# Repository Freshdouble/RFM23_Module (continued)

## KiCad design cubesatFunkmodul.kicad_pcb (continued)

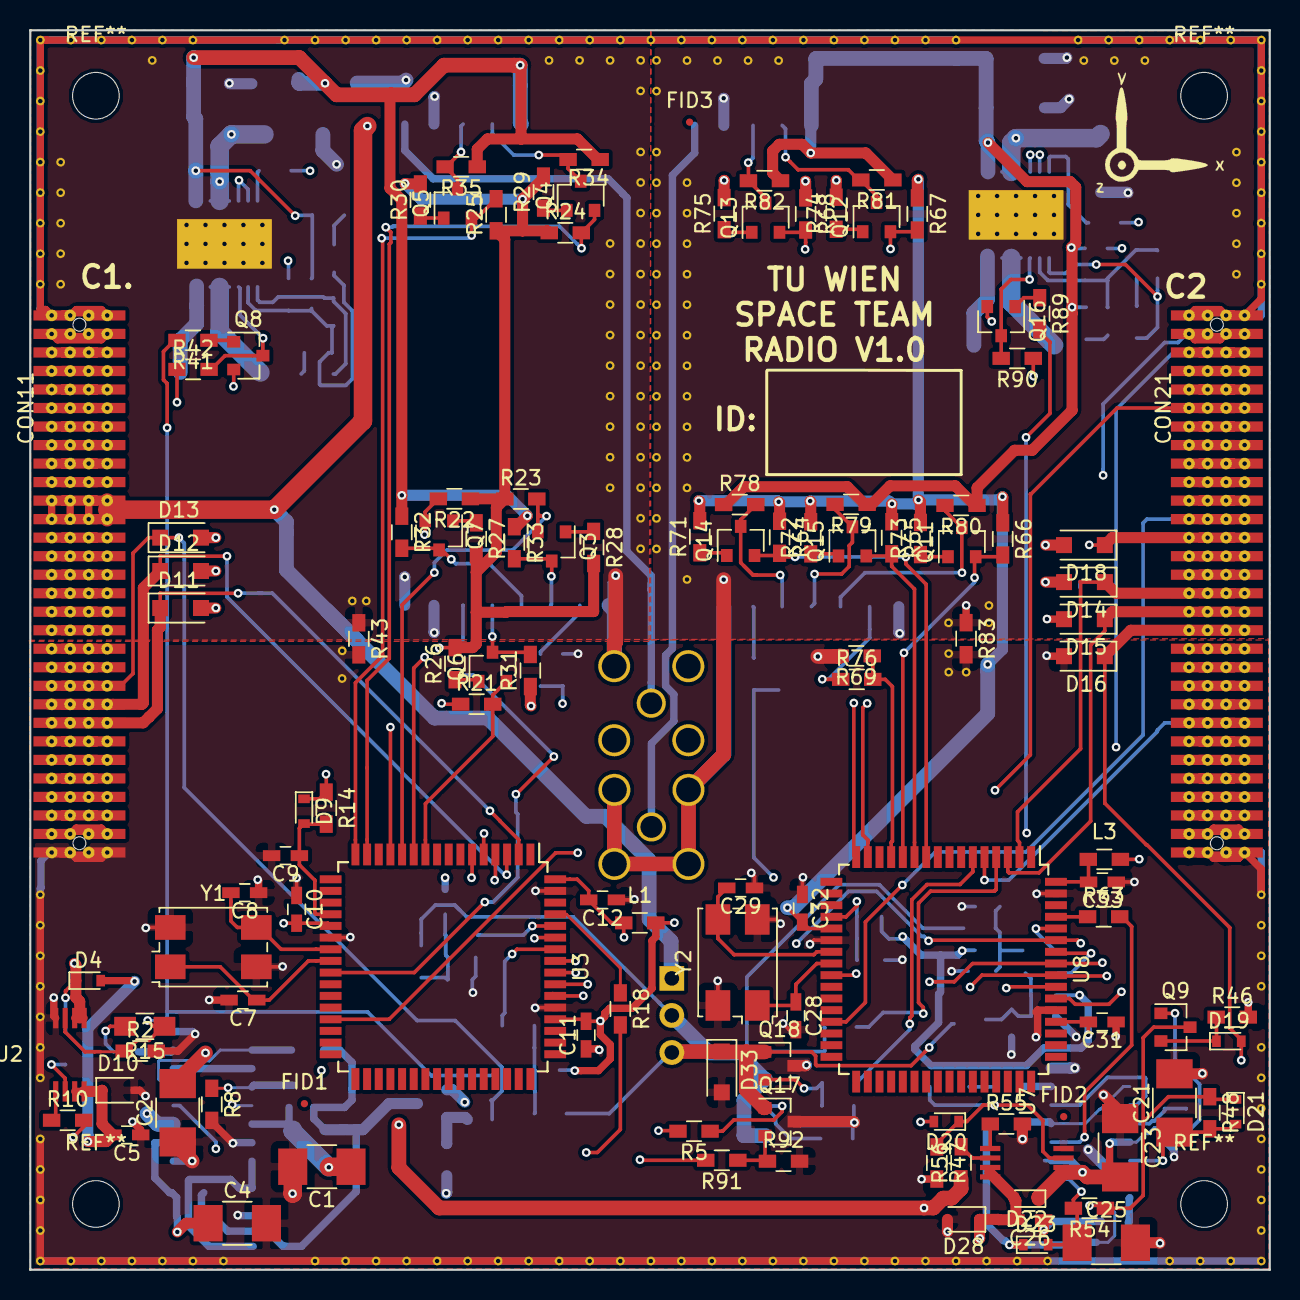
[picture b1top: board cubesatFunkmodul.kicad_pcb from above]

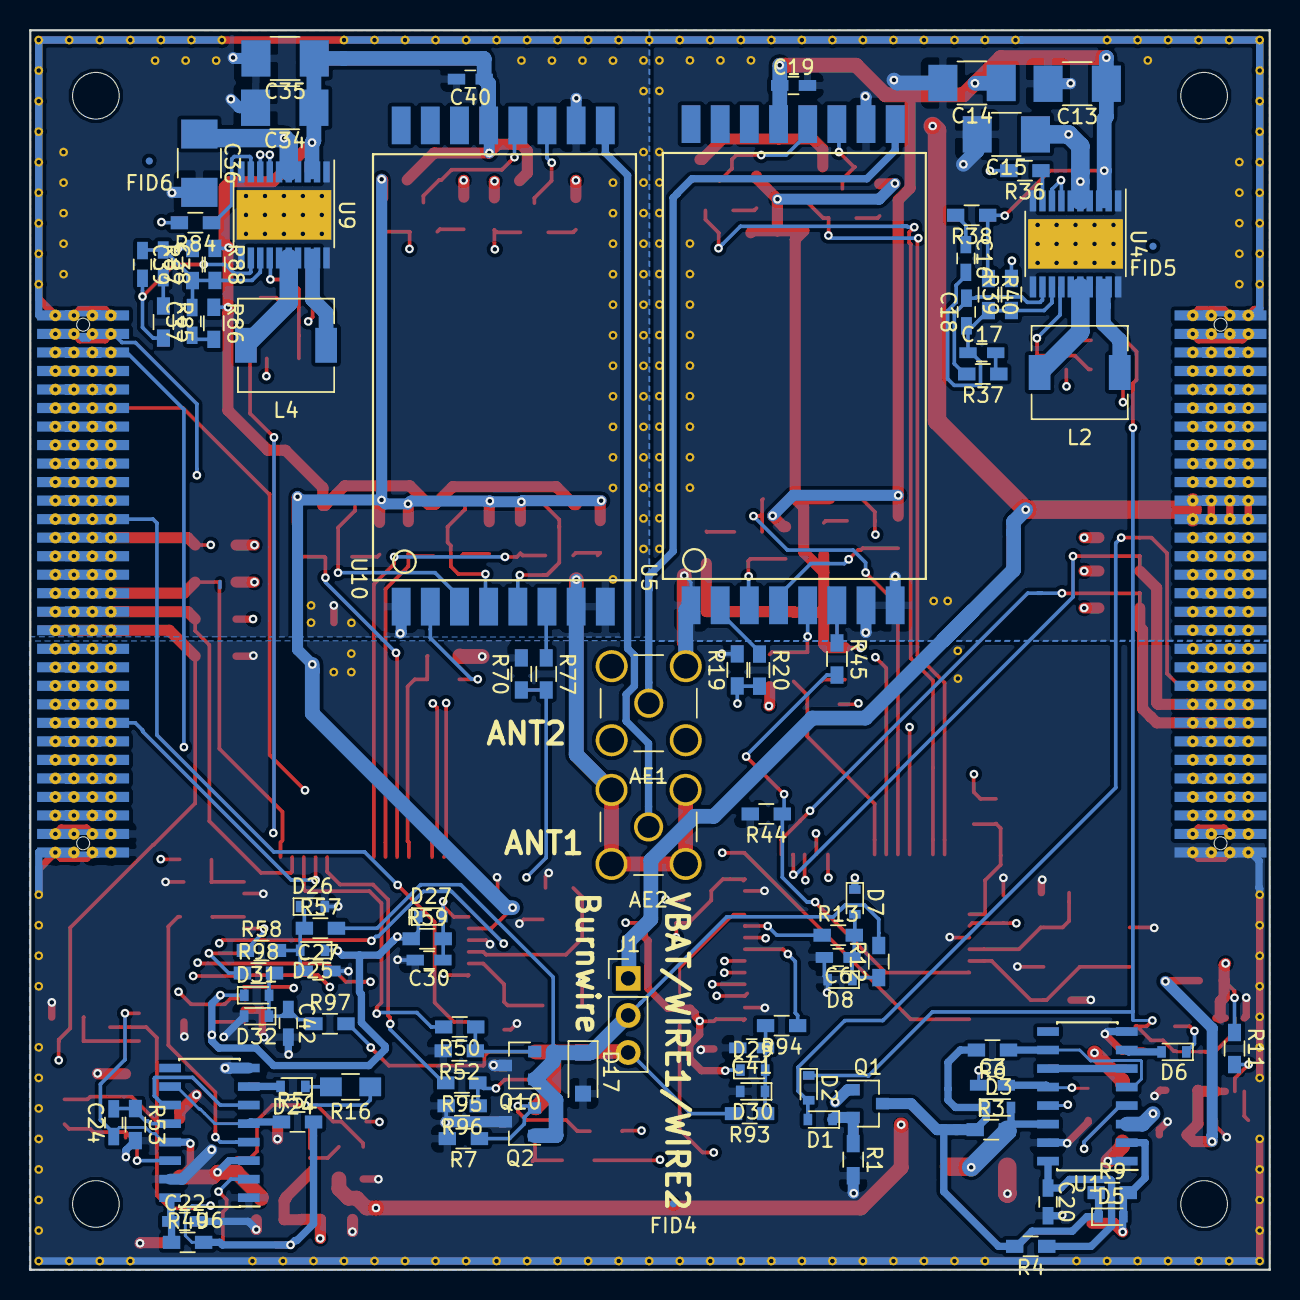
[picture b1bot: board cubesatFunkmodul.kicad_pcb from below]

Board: 4 copper layers, 85.0 x 85.0 mm, 214 parts (96 on the bottom side), 137 nets.

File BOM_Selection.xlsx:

Part | Value | Device | Package | Description | Description2 | Qty | Place_YES/NO | Povided_by_customer_YES/NO | Distributor | Ordernumber | Weblink | Remarks_customer | Unit_price | Total_price | REMARKS_BETA
AE1 AE2 |  |  | SMA_THT |  |  | 2 | NO | YES
C9 C30 | 10nF |  | 0603 |  |  | 2 | YES | NO | Digikey | 311+K2:K26-1085-1-ND | https://www.digikey.at/product-detail/de/yageo/CC0603KRX7R9B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
C10 C11 C12 C5 C6 C20 C41 C19 C31 C32 C33 C26 C27 C22 C42 C40 | 100nF |  | 0603 |  |  | 16 | YES | NO | Digikey | 399-7845-1-ND | https://www.digikey.at/product-detail/de/kemet/C0603C104M5RA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
C7 C8 C28 C29 | 10pF |  | 0603 |  |  | 4 | YES | NO | Digikey | 490-1403-1-ND | https://www.digikey.at/product-detail/de/murata-electronics-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
C2 C23 | 1µF |  | 1210 |  |  | 2 | YES | NO | Digikey | 587-1366-1-ND | https://www.digikey.at/product-detail/de/taiyo-yuden/UMK325B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
C3 C24 | 1nF |  | 0603 |  |  | 2 | YES | NO | Digikey | 478-1215-1-ND | https://www.digikey.at/product-detail/de/avx-corporation/060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
C4 C1 C25 C21 | 10µF |  | 1210 |  |  | 4 | YES | NO | Digikey | 490-1875-1-ND | https://www.digikey.at/product-detail/de/murata-electronics-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
C14 C13 C15 C35 C34 C36 | 47µF |  | 1210 |  |  | 6 | YES | NO | Digikey | 490-6538-1-ND | https://www.digikey.at/product-detail/de/murata-electronics-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
C16 C37 | 47pF |  | 0603 |  |  | 2 | YES | NO | Digikey | 399-6191-1-ND | https://www.digikey.at/product-detail/de/kemet/CBR06C470JAGA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
C18 C39 | 12pF |  | 0603 |  |  | 2 | YES | NO | Digikey | 712-1313-1-ND | https://www.digikey.at/product-detail/de/johanson-technology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
C17 C38 | 680pF |  | 0603 |  |  | 2 | YES | NO | Digikey | 399-7948-1-ND | https://www.digikey.at/product-detail/de/kemet/C0603C681F5GA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
R14 R11 R6 R2 R9 R3 R7 R92 R59 R56 R51 R47 R54 R48 R52 R96 | 100k |  | 0603 |  |  | 16 | YES | NO | Digikey | 311-100KLDCT-ND | https://www.digikey.at/product-detail/de/yageo/AC0603FR-0710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
R10 R55 | 15k |  | 0603 |  |  | 2 | YES | NO | Digikey | RMCF0603JT15K0CT-ND | https://www.digikey.at/product-detail/de/stackpole-electroni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
R8 R12 R13 R93 R94 R19 R21 R22 R23 R24 R25 R31 R32 R33 R34 R35 R42 R41 R44 R53 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 | 10k |  | 0603 |  |  | 38 | YES | NO | Digikey | RMCF0603JT10K0CT-ND | https://www.digikey.at/product-detail/de/stackpole-electroni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
R18 R5 R91 R63 R50 R95 | 100R |  | 0603 |  |  | 6 | YES | NO | Digikey | RMCF0603JT100RCT-ND | https://www.digikey.at/product-detail/de/stackpole-electroni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
R1 R46 | 22k |  | 0603 |  |  | 2 | YES | NO | Digikey | RMCF0603JT22K0CT-ND | https://www.digikey.at/product-detail/de/stackpole-electroni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
R4 R49 | 47R |  | 0603 |  |  | 2 | YES | NO | Digikey | RMCF0603JT47R0CT-ND | https://www.digikey.at/product-detail/de/stackpole-electroni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
R15 R16 | 0R |  | 0805 |  |  | 2 | NO | YES
R20 R26 R27 R28 R29 R30 R45 R76 R71 R72 R73 R74 R75 R77 | 4k7 |  | 0603 |  |  | 14 | YES | NO | Digikey | RMCF0603JT47K0CT-ND | https://www.digikey.at/product-detail/de/stackpole-electroni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
R36 R84 | 90k9 |  | 0603 |  |  | 2 | YES | NO | Digikey | P90.9KHCT-ND | https://www.digikey.at/product-detail/de/panasonic-electroni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
R40 R88 | 887k |  | 0603 |  |  | 2 | YES | NO | Digikey | P16016CT-ND | https://www.digikey.at/product-detail/de/panasonic-electroni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
R39 R87 | 121k |  | 0603 |  |  | 2 | YES | NO | Digikey | 311-2410-1-ND | https://www.digikey.at/product-detail/de/yageo/RT0603DRE0712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
R38 R86 | 6k81 |  | 0603 |  |  | 2 | YES | NO | Digikey | RMCF0603FT6K81CT-ND | https://www.digikey.at/product-detail/de/stackpole-electroni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
R37 R85 | 49k9 |  | 0603 |  |  | 2 | YES | NO | Digikey | RMCF0603FT49K9CT-ND | https://www.digikey.at/product-detail/de/stackpole-electroni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
R43 R83 | 0R |  | 0603 |  |  | 2 | YES | NO | Digikey | P0.0GCT-ND | https://www.digikey.at/product-detail/de/panasonic-electroni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
D9 D4 D1 D2 D6 D3 D5 D8 D7 D30 D29 D27 D22 D19 D20 D24 D21 D23 D26 D25 D32 D31 |  |  | 0603 |  |  | 22 | YES | NO | Digikey | TS4148C RZGCT-ND | https://www.digikey.at/product-detail/de/taiwan-semiconducto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
D10 D28 |  |  | SOD-323F |  |  | 2 | YES | NO | Digikey | DZ2J036M0LCT-ND | https://www.digikey.at/products/de?keywords=DZ2J036M0LCT-ND
D11 D12 D13 D14 D15 D16 D17 D18 D33 |  |  | SOD-123F |  |  | 9 | YES | NO | Digikey | F7701CT-ND | https://www.digikey.at/product-detail/de/littelfuse-inc/SMF3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
L1 L3 | 10nH |  | 0603 |  |  | 2 | YES | NO | Digikey | 1276-6306-1-ND | https://www.digikey.at/product-detail/de/samsung-electro-mec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
L2 L4 | 5µH |  | L_6.3x6.3_H3 |  |  | 2 | YES | NO | Digikey | 308-2073-2-ND | https://www.digikey.at/product-detail/de/sumida-america-comp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
Q2 Q17 Q10 Q18 |  |  | SOT-23 |  |  | 4 | YES | NO | Digikey | 785-1009-1-ND | https://www.digikey.at/product-detail/de/alpha-omega-semicon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
Q1 Q9 |  |  | SOT-23 |  |  | 2 | YES | NO | Digikey | SSM3J334RLFTR-ND | https://www.digikey.at/products/de?keywords=SSM3J334RLFTR-ND
Q6 Q7 Q3 Q4 Q5 Q8 Q14 Q15 Q11 Q12 Q13 Q16 |  |  | SOT-23 |  |  | 12 | YES | NO | Digikey | MMBT5551-TPTR-ND | https://www.digikey.at/product-detail/de/micro-commercial-co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
U3 U8 |  |  | TQFP64 |  |  | 2 | YES | NO | Digikey | ATMEGA128-16AURCT-ND | https://www.digikey.at/product-detail/de/microchip-technolog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
U2 U7 |  |  | µMax8 |  |  | 2 | YES | NO | Digikey | MAX892LEUA+-ND | https://www.digikey.at/product-detail/de/maxim-integrated/MA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
U1 U6 |  |  | SOIC16 |  |  | 2 | YES | NO | Digikey | MC74HC4538ADR2GOSCT-ND | https://www.digikey.at/product-detail/de/on-semiconductor/MC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
U4 U9 |  |  | TSSOP 20 |  |  | 2 | YES | NO | Digikey | LTC3113IFE#PBF-ND | https://www.digikey.at/product-detail/de/linear-technology/L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
U5 U10 |  |  | RFM23BP |  |  | 2 | NO | YES
Y1 Y2 |  |  | Crystal_SMD_7050-4pin_7.0x5.0mm |  |  | 2 | YES | NO | Digikey | 407F39D007M3728-ND | https://www.digikey.at/products/de?keywords=407F39D007M3728
CON11 CON21 |  |  |  |  |  | 2 | YES | NO | Digikey | FTS-130-03-L-DV-SA-ND | https://www.digikey.at/product-detail/de/samtec-inc/FTS-130-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 | Place on Toplayer
CON11 CON21 |  |  |  |  |  | 2 | YES | NO | Digikey | CLP-130-02-F-D-A-ND | https://www.digikey.at/product-detail/de/samtec-inc/CLP-130-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 | Place on Bottomlayer

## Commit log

2017-08-15 Adds new values
2017-08-15 Cleares PCB
2017-08-16 Adds new submodules
2017-08-23 Implements stepup dc/dc
2017-09-12 Adds new Modules and WDT Circuit
    - Added Schematic for MAX892 Highside Switch
    - Added Schematic for MC74HC4538A
    - Constructed Watchdogtimer Circuit to Reset µC and Radiomodule
2017-09-20 Adds ESD Protection and finalisation of wdt
2017-09-23 Adds RFM23BP Module to Bib and Layout
2017-09-25 Adds component names
2017-10-04 Change Diodes to STTH102A
    Datasheet:
    http://www.st.com/content/ccc/resource/technical/document/datasheet/98/bc/9f/6f/26/c3/4e/73/CD00002613.pdf/files/CD00002613.pdf/jcr:content/translations/en.CD00002613.pdf
2017-10-08 Auto stash before merge of "master" and "github/master"
2017-10-08 Adds Connectors
2017-10-09 Adds RFM23BP Footprint and places module on board
2017-10-11 Adds Levelshifter for NIRQ
2017-10-16 Layout Module1 prefinish
    Modules Placed
    Ground Plane placed
    Supply Plane placed
    TODO: Add cubesat connector, Place Antenna connector, Place burnwire connector, Review
2017-10-25 Adds Cubesat Connector to Layout
2017-10-25 Replaces Q1 with p channel mosfet
2017-10-29 Resolves Bug in Cubesat Connector Library
2017-11-02 Integrates Connectors in Design
    Beginn to add mounting holes
2017-11-05 Adds new unit
2017-11-08 Places µC of second module
2017-11-13 Places all Components of second module
2017-11-13 Moved rf module to bottom layer
2017-11-14 Adds second burnwire fets
2017-11-15 Fixes some drc violations
2017-11-16 Adds SMA and Burnwire connectors
2017-11-17 Adds stiching vias
2017-11-17 Adds BOM and production files
2017-11-17 Adds inductor type to schematic
2017-11-17 Adds via for shorter ground return path
2017-11-17 Closes Ground Ring
2017-11-20 Adds Coordinatesystem and bom selection
2017-11-29 Places fiducial markers
2017-12-04 Updates BOM List
2017-12-05 Auto stash before merge of "master" and "origin/master"
2017-12-05 Adds Fiducials to pick and place data
2017-12-06 Deletes unused position files
2017-12-06 Formats pick and place data
2017-12-19 Prepares top fab layer for fabricationplan output
2018-01-05 Adds component scheme
2018-01-05 Bugfix for external watchdog circuit
2018-01-16 Changes to get in production
    - Adds connector outlines to component scheme
    - Changes crystalcapacitors to 15pF
    - Regenerated top and bottom component scheme
    - Adds formated BOM list for betalayout
2018-02-08 Updates pick and place file
2018-04-20 Adds pin connection description
2019-05-15 Converted to new kicad version
